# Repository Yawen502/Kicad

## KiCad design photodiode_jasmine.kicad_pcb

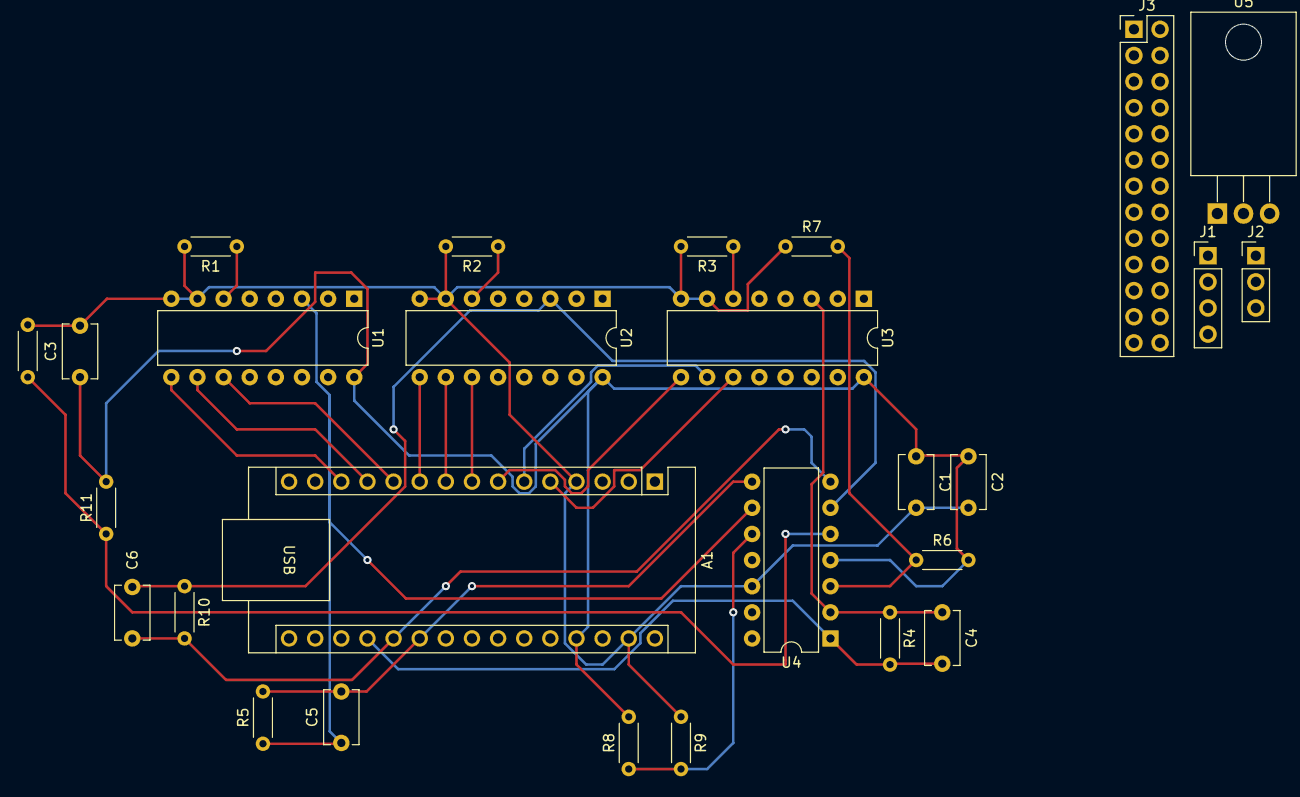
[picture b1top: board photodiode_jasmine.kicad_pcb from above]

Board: 2 copper layers, 27 parts (0 on the bottom side), 51 nets.

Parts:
A1: Arduino_Nano_Every; Arduino_Nano
C1, C2, C3: 0.1u; C_Disc_D5.1mm_W3.2mm_P5.00mm
C4, C5, C6: 20pF; C_Disc_D5.1mm_W3.2mm_P5.00mm
J1: Conn_01x04_Pin; PinHeader_1x04_P2.54mm_Vertical
J2: Conn_01x03_Pin; PinHeader_1x03_P2.54mm_Vertical
J3: Conn_02x13_Top_Bottom; PinHeader_2x13_P2.54mm_Vertical
R1, R2, R3, R7, R9, R12: 10k; R_Axial_DIN0204_L3.6mm_D1.6mm_P5.08mm_Horizontal
R4, R5, R10: 100k; R_Axial_DIN0204_L3.6mm_D1.6mm_P5.08mm_Horizontal
R6, R8, R11: 1M; R_Axial_DIN0204_L3.6mm_D1.6mm_P5.08mm_Horizontal
U1, U2, U3: 74HCT4051; DIP-16_W7.62mm
U4: MCP6004; DIP-14_W7.62mm
U5: L7805; TO-220-3_Horizontal_TabDown

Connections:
+5V: A1.27 (+5V), C1.1, C2.1, C3.1, R6.2, R8.2, R11.2, U1.16 (VCC), U2.16 (VCC), U3.16 (VCC), U4.4 (V+)
+5VP: J2.1, U5.3 (OUT)
+12V: A1.30 (VIN), J1.1, U5.1 (IN)
/Amp/Mux1SelA: A1.5 (D2), U3.11 (S0)
/Amp/Mux1SelB: A1.6 (D3), U3.10 (S1)
/Amp/Mux1SelC: A1.7 (D4), U3.9 (S2)
/Amp/Mux2SelA: A1.8 (D5), U2.11 (S0)
/Amp/Mux2SelB: A1.9 (D6), U2.10 (S1)
/Amp/Mux2SelC: A1.10 (D7), U2.9 (S2)
/Amp/Mux3SelA: A1.11 (D8), U1.11 (S0)
/Amp/Mux3SelB: A1.12 (D9), U1.10 (S1)
/Amp/Mux3SelC: A1.13 (D10), U1.9 (S2)
/Amp/PhotodiodesMuxed1/Out: C4.1, R4.1, U3.3 (A), U4.2 (-)
/Amp/PhotodiodesMuxed2/Out: C5.1, R5.1, U1.3 (A), U4.9 (-)
/Amp/PhotodiodesMuxed3/Out: C6.1, R10.1, U2.3 (A), U4.6 (-)
/LED_Data: A1.14 (MOSI), J2.2
/Out1: A1.19 (A0), C4.2, R4.2, U4.1
/Out2: A1.20 (A1), C6.2, R10.2, U4.7
/Out3: A1.21 (A2), C5.2, R5.2, U4.8
GND: A1.4 (GND), A1.29 (GND), C1.2, C2.2, C3.2, J1.4, J2.3, J3.13, J3.26, R1.2, R2.2, R3.2, R7.1, R9.1, R12.1, U1.7 (VEE), U1.8 (GND), U2.7 (VEE), U2.8 (GND), U3.7 (VEE), U3.8 (GND), U4.11 (V-), U4.12 (+), U5.2 (GND)
unnamed: R1.1, U1.6 (~E)
unnamed: R2.1, U2.6 (~E)
unnamed: R3.1, U3.6 (~E)
unnamed: R6.1, R7.2, U4.3 (+)
unnamed: R11.1, R12.2, U4.5 (+)
unnamed: R8.1, R9.2, U4.10 (+)
unnamed: U4.13 (-), U4.14
PD1: J3.1, U3.13 (A0)
PD2: J3.2, U3.14 (A1)
PD3: J3.3, U3.15 (A2)
PD4: J3.4, U3.12 (A3)
PD5: J3.5, U3.1 (A4)
PD6: J3.6, U3.5 (A5)
PD7: J3.7, U3.2 (A6)
PD8: J3.8, U3.4 (A7)
PD9: J3.9, U1.13 (A0)
PD10: J3.10, U1.14 (A1)
PD11: J3.11, U1.15 (A2)
PD12: J3.12, U1.12 (A3)
PD13: J3.14, U1.1 (A4)
PD14: J3.15, U1.5 (A5)
PD15: J3.16, U1.2 (A6)
PD16: J3.17, U1.4 (A7)
PD17: J3.18, U2.13 (A0)
PD18: J3.19, U2.14 (A1)
PD19: J3.20, U2.15 (A2)
PD20: J3.21, U2.12 (A3)
PD21: J3.22, U2.1 (A4)
PD22: J3.23, U2.5 (A5)
PD23: J3.24, U2.2 (A6)
PD24: J3.25, U2.4 (A7)

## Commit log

2023-05-31 Added photodiode connector, haven't routed
2023-05-31 Add connectors, routed
2023-05-31 Not sure what's changed
2023-06-29 Created using Colaboratory
